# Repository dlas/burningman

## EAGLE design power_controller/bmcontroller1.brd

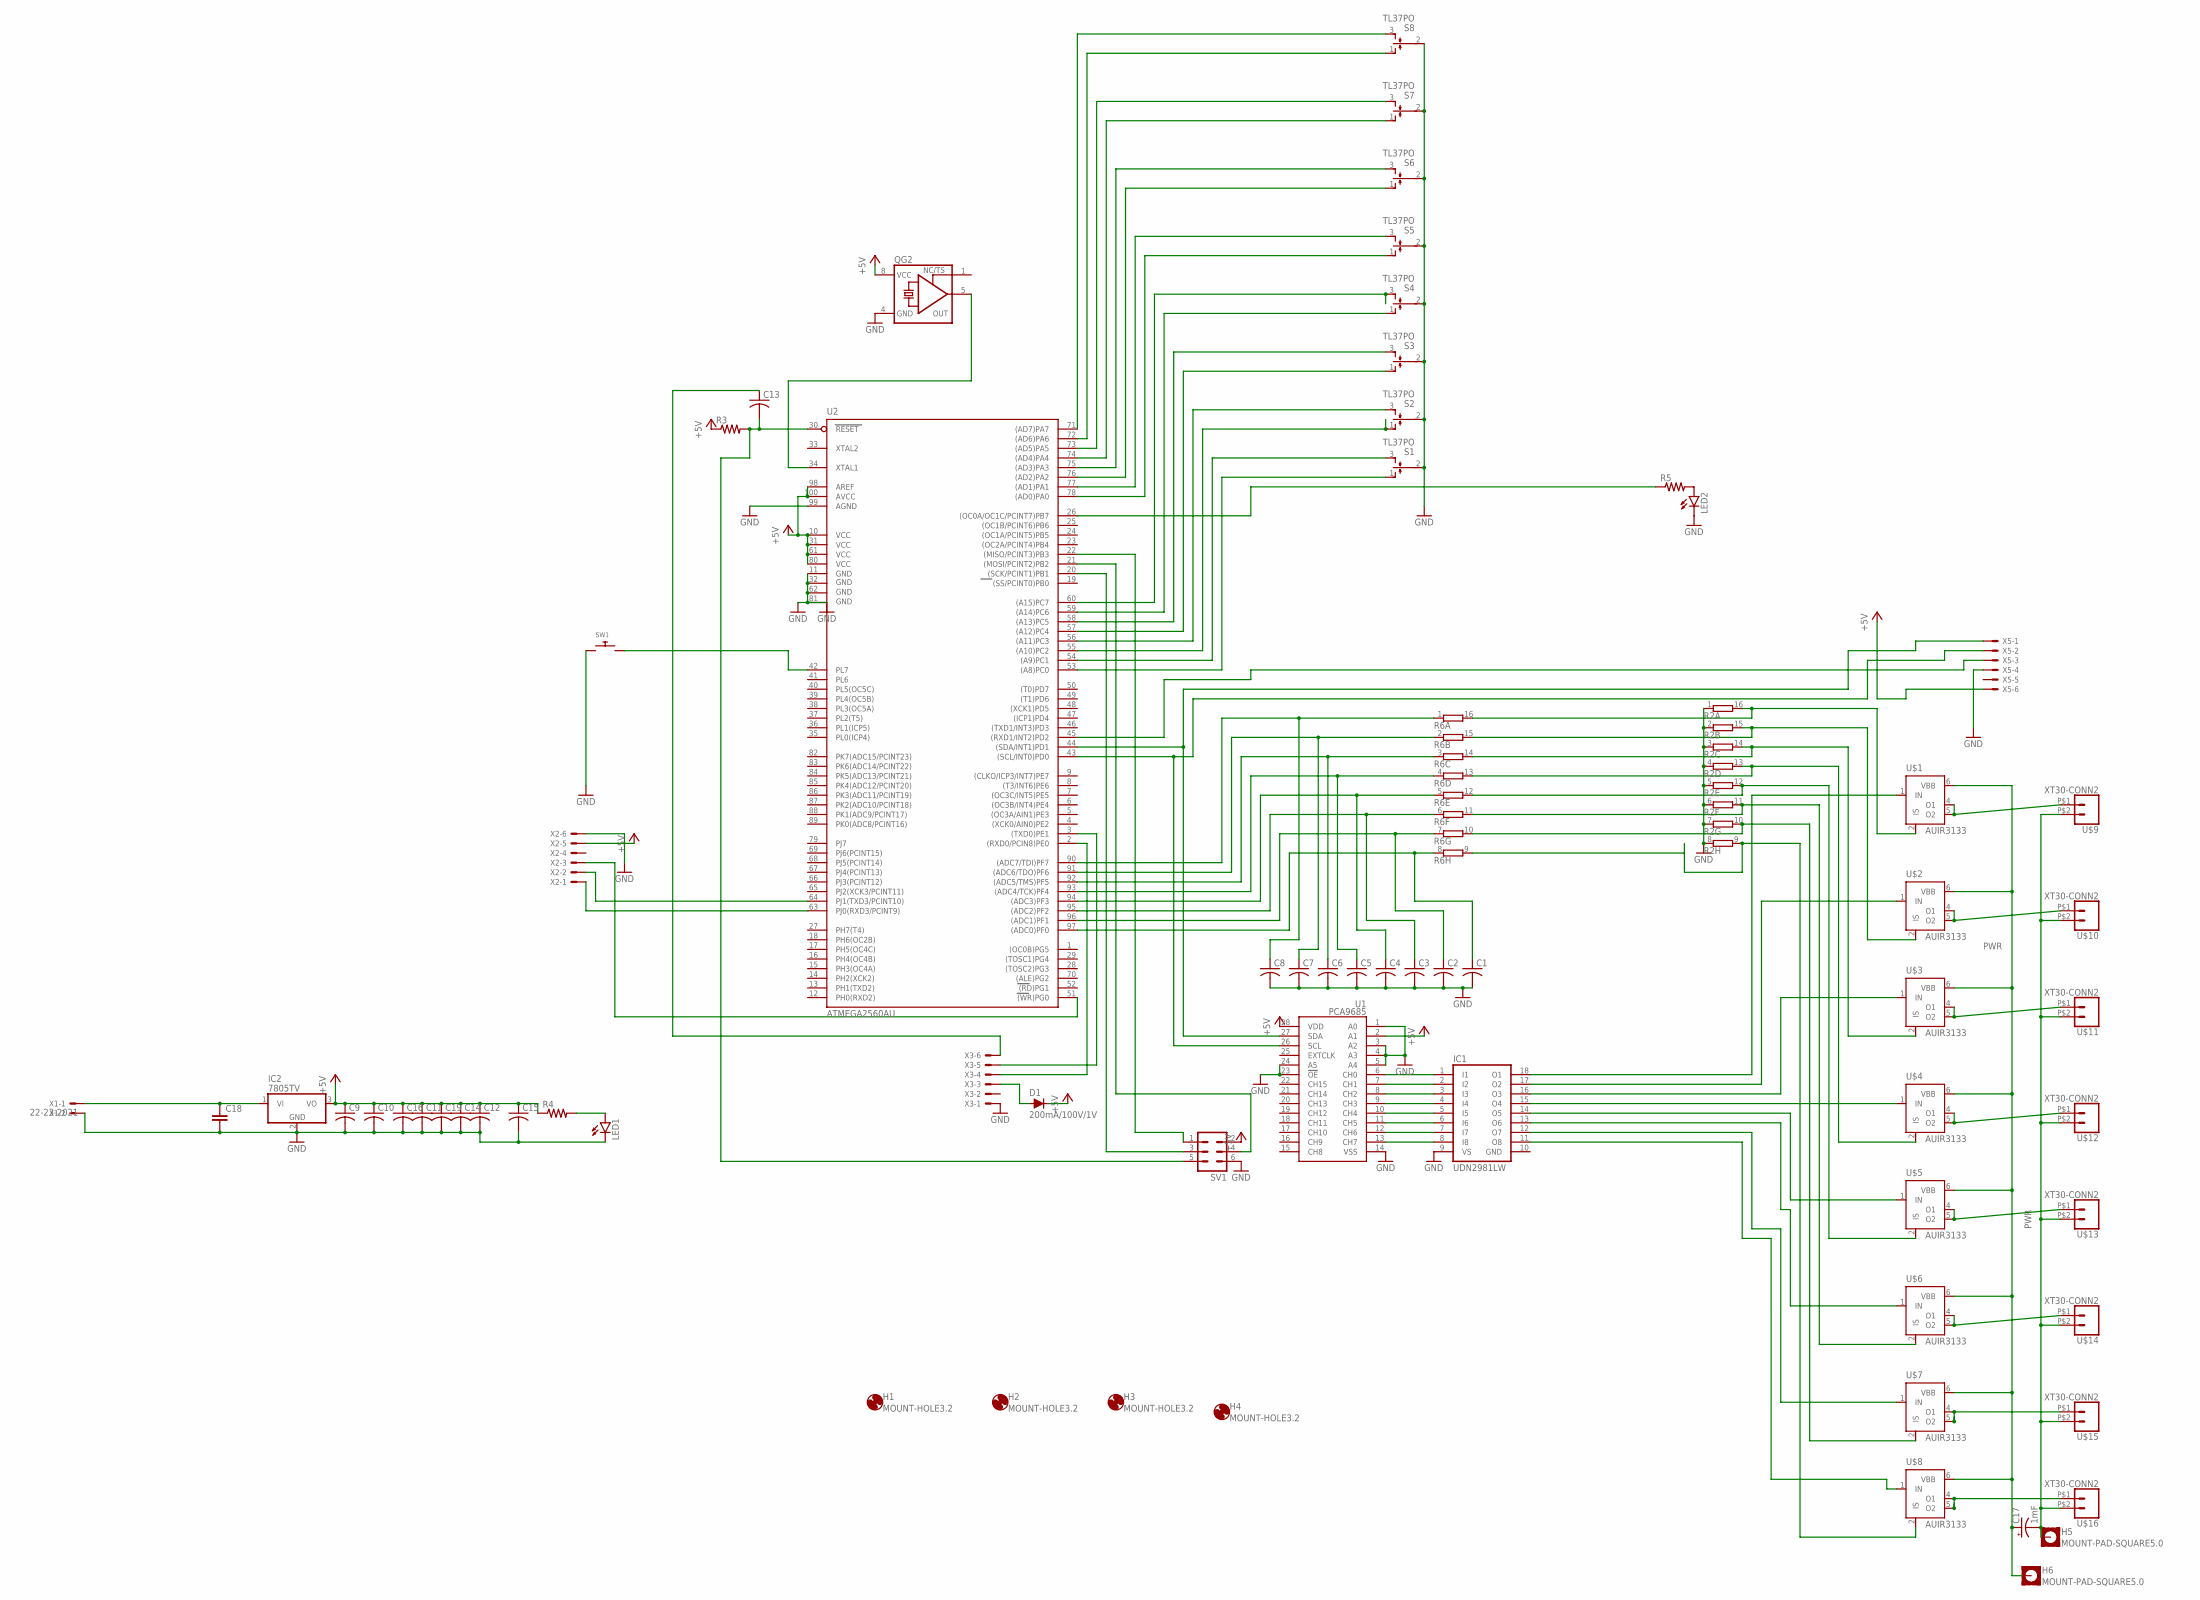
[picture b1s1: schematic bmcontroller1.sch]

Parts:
C1, C2, C3, C4, C5, C6, C7, C8, C9, C19: C-USC0805; C0805
C10, C11, C12, C13, C14, C15, C16: C-US025-024X044; C025-024X044
C17: 1mF; CPOL-RADIAL-5MM-10MM
C18: C2,5-3; C2.5-3
D1: 200mA/100V/1V; DIODE-1N4148
H1, H2, H3, H4: MOUNT-HOLE3.2; 3,2
H5, H6: MOUNT-PAD-SQUARE5.0; 5,0-PAD-SQUARE
IC1: UDN2981LW; SO18W
IC2: 7805TV; TO220V
LED1, LED2: LED3MM
QG2: XO-8; DIL08S
R2, R6: 4816P-T01E; 4816P
R3, R4, R5: R-US_R0805; R0805
S1, S2, S3, S4, S5, S6, S7, S8: TL37PO; TL3XPO
SV1: MA03-2
SW1: SWITCH_PUSHBUTTONEVQ-PE; TACT_PANA-EVQ
U1: PCA9685; TSSOP-28_4MM
U2: ATMEGA2560AU; TQFP100
U$1, U$2, U$3, U$4, U$5, U$6, U$7, U$8: AUIR3133; TO263-51
U$9, U$10, U$11, U$12, U$13, U$14, U$15, U$16: XT30-CONN2; XT30-2
X1: 22-23-2021
X2, X3, X5: 22-23-2061

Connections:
+5V: C9.1, C10.1, C11.1, C12.1, C14.1, C15.1, C16.1, C19.1, D1.C, IC2.3 (VO), QG2.8 (VCC), R3.1, R4.1, SV1.2, U1.2 (A1), U1.28 (VDD), U2.10 (VCC), U2.31 (VCC1), U2.61 (VCC2), U2.80 (VCC3), U2.98 (AREF), U2.100 (AVCC), X2.5, X5.6
BIGGND: C17.-, H5.B5, U$9.P$2 (2), U$10.P$2 (2), U$11.P$2 (2), U$12.P$2 (2), U$13.P$2 (2), U$14.P$2 (2), U$15.P$2 (2), U$16.P$2 (2)
GND: C1.2, C2.2, C3.2, C4.2, C5.2, C6.2, C7.2, C8.2, C9.2, C10.2, C11.2, C12.2, C14.2, C15.2, C16.2, C18.2, C19.2, IC1.9 (VS), IC1.10 (GND), IC2.2 (GND), LED1.K (C), LED2.K (C), QG2.4 (GND), R2.1, R2.2 (1), R2.3 (1), R2.4 (1), R2.5 (1), R2.6 (1), R2.7 (1), R2.8 (1), S1.2, S2.2, S3.2, S4.2, S5.2, S6.2, S7.2, S8.2, SV1.6, SW1.P$1, U1.1 (A0), U1.3 (A2), U1.4 (A3), U1.5 (A4), U1.14 (VSS), U1.23 (!OE), U1.24 (A5), U2.11 (GND), U2.32 (GND1), U2.62 (GND2), U2.81 (GND3), U2.99 (AGND), X1.2, X2.6, X3.1, X5.4
unnamed: C8.1, R6.1, U2.90 ((ADC7/TDI)PF7)
unnamed: C7.1, R6.2 (1), U2.91 ((ADC6/TDO)PF6)
unnamed: C6.1, R6.3 (1), U2.92 ((ADC5/TMS)PF5)
unnamed: C5.1, R6.4 (1), U2.93 ((ADC4/TCK)PF4)
unnamed: C4.1, R6.5 (1), U2.94 ((ADC3)PF3)
unnamed: C3.1, R6.6 (1), U2.95 ((ADC2)PF2)
unnamed: C2.1, R6.7 (1), U2.96 ((ADC1)PF1)
unnamed: C1.1, R6.8 (1), U2.97 ((ADC0)PF0)
unnamed: S8.1 (O), U2.72 ((AD6)PA6)
unnamed: IC1.18 (O1), U$1.1 (IN)
unnamed: IC1.14 (O5), U$5.1 (IN)
unnamed: IC1.1 (I1), U1.6 (CH0)
unnamed: R2.13 (2), R6.13 (2), U$4.2 (IS)
unnamed: R2.12 (2), R6.12 (2), U$5.2 (IS)
unnamed: R2.11 (2), R6.11 (2), U$6.2 (IS)
unnamed: R2.10 (2), R6.10 (2), U$7.2 (IS)
unnamed: R5.1, U2.26 ((OC0A/OC1C/PCINT7)PB7)
unnamed: R2.9 (2), R6.9 (2), U$8.2 (IS)
unnamed: IC1.2 (I2), U1.7 (CH1)
unnamed: IC1.3 (I3), U1.8 (CH2)
unnamed: IC1.4 (I4), U1.9 (CH3)
unnamed: QG2.5 (OUT), U2.34 (XTAL1)
unnamed: D1.A, X3.3
unnamed: S2.1 (O), U2.55 ((A10)PC2)
unnamed: C18.1, IC2.1 (VI), X1.1
unnamed: IC1.5 (I5), U1.10 (CH4)
unnamed: S4.3 (S), U2.60 ((A15)PC7)
unnamed: S8.3 (S), U2.71 ((AD7)PA7)
unnamed: SW1.P$2, U2.42 (PL7)
unnamed: S7.3 (S), U2.73 ((AD5)PA5)
unnamed: S7.1 (O), U2.74 ((AD4)PA4)
unnamed: S6.3 (S), U2.75 ((AD3)PA3)
unnamed: S6.1 (O), U2.76 ((AD2)PA2)
unnamed: LED1.A, R4.2
unnamed: C13.2, R3.2, SV1.5, U2.30 (RESET)
unnamed: SV1.1, U2.22 ((MISO/PCINT3)PB3)
unnamed: SV1.3, U2.20 ((SCK/PCINT1)PB1)
unnamed: SV1.4, U2.21 ((MOSI/PCINT2)PB2)
unnamed: C13.1, X3.6
unnamed: U2.3 ((TXD0)PE1), X3.5
unnamed: U2.2 ((RXD0/PCIN8)PE0), X3.4
unnamed: U$8.4 (O1), U$8.5 (O2), U$16.P$1 (1)
unnamed: U1.27 (SDA), U2.44 ((SDA/INT1)PD1), X5.1
unnamed: U2.63 (PJ0(RXD3/PCINT9)), X2.1
unnamed: U2.64 (PJ1(TXD3/PCINT10)), X2.2
unnamed: U2.51 ((WR)PG0), X2.3
unnamed: U1.26 (SCL), U2.43 ((SCL/INT0)PD0), X5.2
unnamed: U2.45 ((RXD1/INT2)PD2), X5.3
unnamed: U$7.4 (O1), U$7.5 (O2), U$15.P$1 (1)
unnamed: U$6.4 (O1), U$6.5 (O2), U$14.P$1 (1)
unnamed: U$5.4 (O1), U$5.5 (O2), U$13.P$1 (1)
unnamed: U$4.4 (O1), U$4.5 (O2), U$12.P$1 (1)
unnamed: U$3.4 (O1), U$3.5 (O2), U$11.P$1 (1)
unnamed: U$2.4 (O1), U$2.5 (O2), U$10.P$1 (1)
unnamed: U$1.4 (O1), U$1.5 (O2), U$9.P$1 (1)
unnamed: IC1.6 (I6), U1.11 (CH5)
unnamed: IC1.7 (I7), U1.12 (CH6)
unnamed: IC1.16 (O3), U$3.1 (IN)
unnamed: R2.14 (2), R6.14 (2), U$3.2 (IS)
unnamed: R2.15 (2), R6.15 (2), U$2.2 (IS)
unnamed: R2.16 (2), R6.16 (2), U$1.2 (IS)
unnamed: IC1.17 (O2), U$2.1 (IN)
unnamed: IC1.8 (I8), U1.13 (CH7)
unnamed: LED2.A, R5.2
unnamed: IC1.11 (O8), U$8.1 (IN)
unnamed: IC1.12 (O7), U$7.1 (IN)
unnamed: IC1.13 (O6), U$6.1 (IN)
unnamed: IC1.15 (O4), U$4.1 (IN)
unnamed: S5.3 (S), U2.77 ((AD1)PA1)
unnamed: S5.1 (O), U2.78 ((AD0)PA0)
unnamed: S4.1 (O), U2.59 ((A14)PC6)
unnamed: S3.3 (S), U2.58 ((A13)PC5)
unnamed: S3.1 (O), U2.57 ((A12)PC4)
unnamed: S2.3 (S), U2.56 ((A11)PC3)
unnamed: S1.3 (S), U2.54 ((A9)PC1)
unnamed: S1.1 (O), U2.53 ((A8)PC0)
PWR: C17.+, H6.B5, U$1.6 (VBB), U$2.6 (VBB), U$3.6 (VBB), U$4.6 (VBB), U$5.6 (VBB), U$6.6 (VBB), U$7.6 (VBB), U$8.6 (VBB)

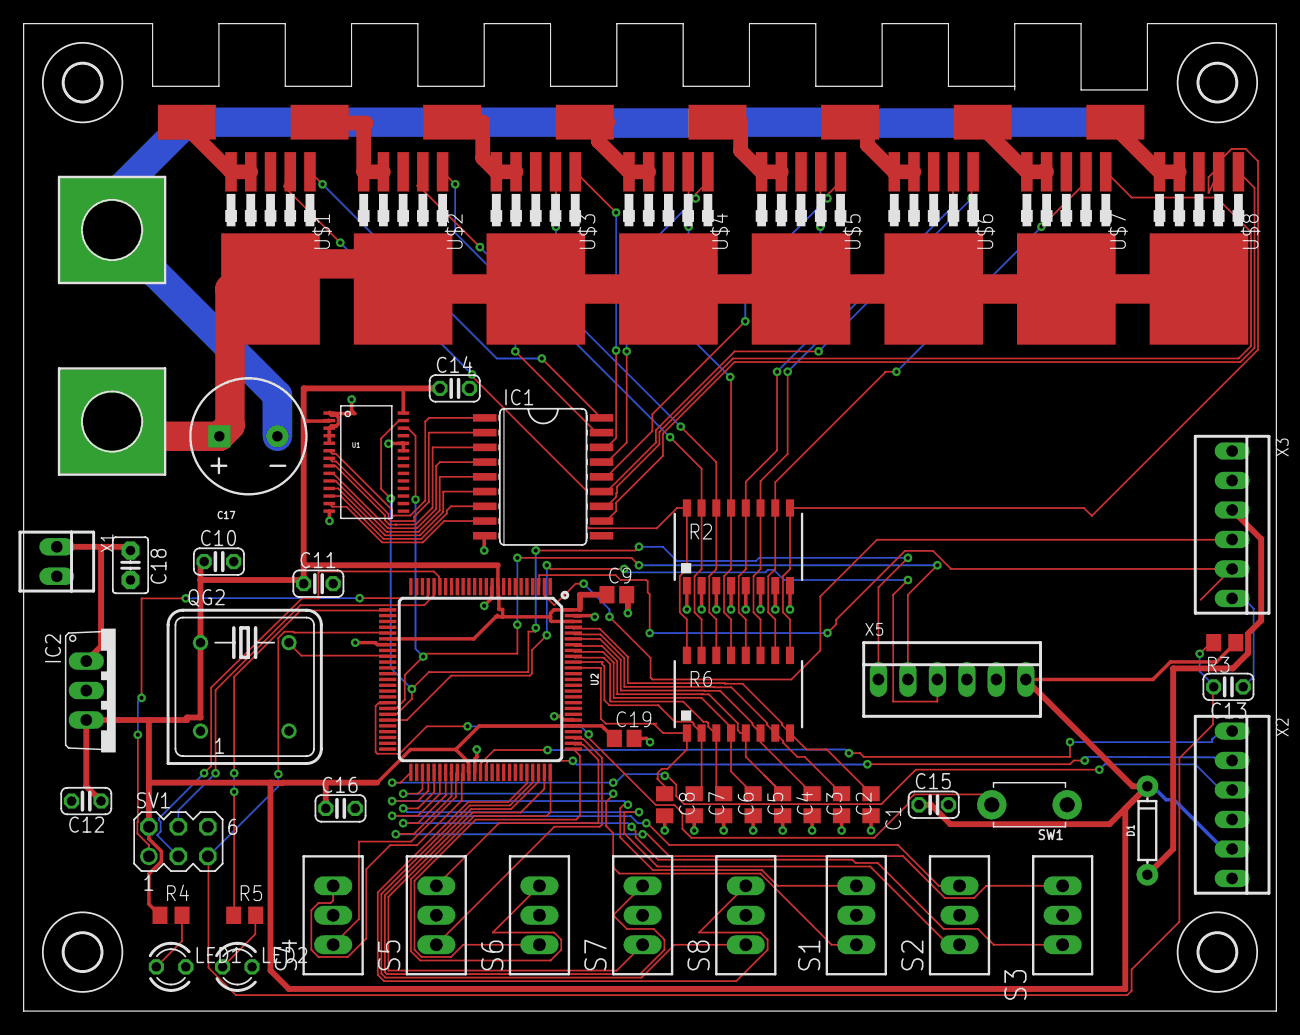
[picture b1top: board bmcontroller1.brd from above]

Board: 2 copper layers, 108.0 x 85.1 mm, 68 parts (0 on the bottom side), 80 nets.

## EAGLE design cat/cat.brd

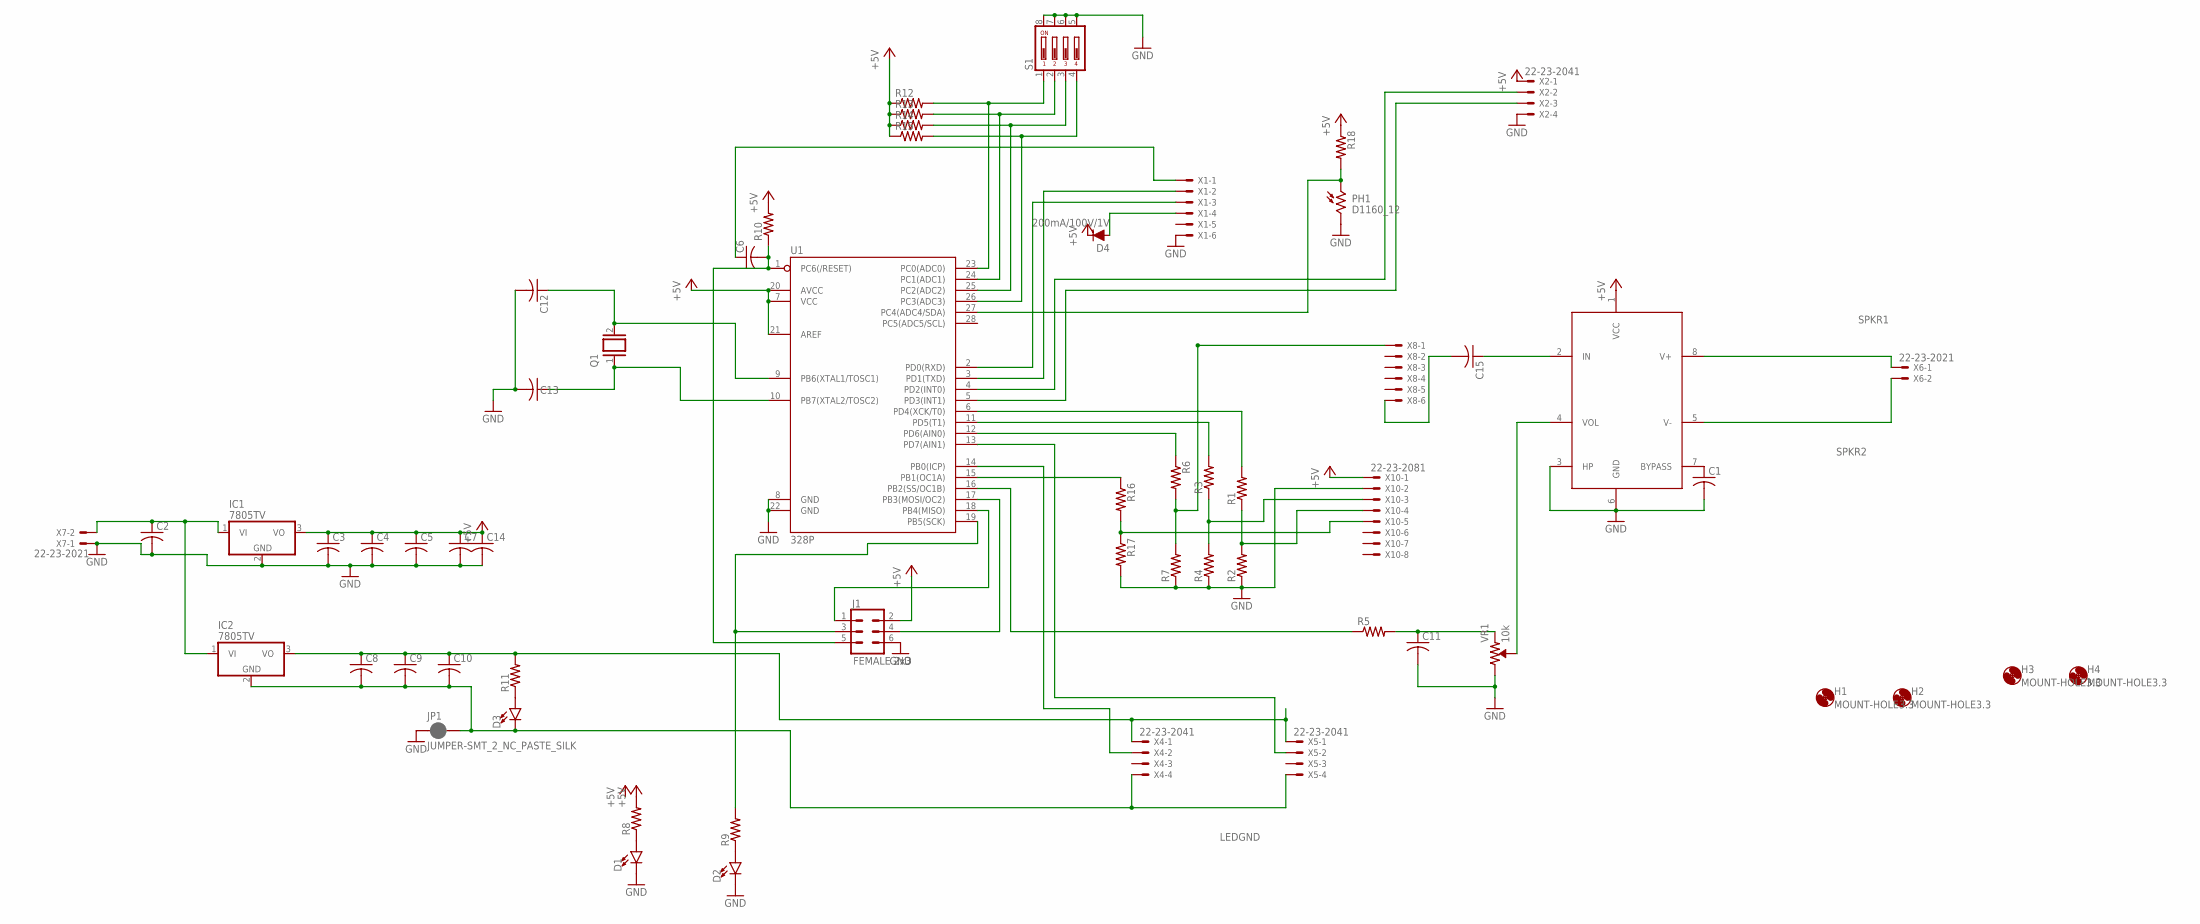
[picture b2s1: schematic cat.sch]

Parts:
C1, C2, C3, C4, C5, C6, C7, C8, C9, C10, C11, C12, C13, C14, C15: C-US025-024X044; C025-024X044
D1, D2, D3: LED-3MM-NO_SILK; LED_3MM-NS
D4: 200mA/100V/1V; DIODE-1N4148
H1, H2, H3, H4: MOUNT-HOLE3.3; 3,3
IC1, IC2: 7805TV; TO220V
J1: FEMALE 2x3; 2X3
JP1: JUMPER-SMT_2_NC_PASTE_SILK; SMT-JUMPER_2_NC_PASTE_SILK
PH1: D1160_12; D11XX
Q1: XTAL/S; QS
R1, R2, R3, R4, R5, R6, R7, R8, R9, R10, R11, R12, R13, R14, R15, R16, R17, R18: R-US_R0805; R0805
S1: DIP04YL
U1: 328P; DIP28
U$1: LM4875; SO8
VR1: 10k; TRIMPOT-PTH-3386U
X1, X8: 22-23-2061
X2, X4, X5: 22-23-2041
X6, X7: 22-23-2021
X10: 22-23-2081

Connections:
+5V: C3.1, C4.1, C5.1, C7.1, C14.1, D4.C, IC1.3 (VO), J1.2, R8.2, R10.2, R12.1, R13.1, R14.1, R15.1, R18.1, U1.7 (VCC), U1.20 (AVCC), U1.21 (AREF), U$1.1 (VCC), X2.1, X10.1
GND: C1.2, C2.2, C3.2, C4.2, C5.2, C7.2, C11.2, C12.2, C13.2, C14.2, D1.K (C), D2.K (C), IC1.2 (GND), J1.6, JP1.1, PH1.2, R2.1, R4.1, R7.1, R17.2, S1.5, S1.6, S1.7, S1.8, U1.8 (GND), U1.22 (GND), U$1.3 (HP), U$1.6 (GND), VR1.3 (CW), X1.6, X2.4, X7.1, X10.2
INPWR: C2.1, IC1.1 (VI), IC2.1 (VI), X7.2
LEDGND: C8.2, C9.2, C10.2, D3.K (C), IC2.2 (GND), JP1.2, X4.4, X5.4
LEDPWR: C8.1, C9.1, C10.1, IC2.3 (VO), R11.2, X4.1, X5.1
unnamed: R1.1, R2.2, X10.4
unnamed: R1.2, U1.6 (PD4(XCK/T0))
unnamed: R3.2, U1.11 (PD5(T1))
unnamed: C15.2, X8.6
unnamed: R3.1, R4.2, X10.3
unnamed: R6.2, R7.2, X8.1
unnamed: J1.3, R9.2, U1.19 (PB5(SCK))
unnamed: R6.1, U1.12 (PD6(AIN0))
unnamed: J1.1, U1.18 (PB4(MISO))
unnamed: J1.4, U1.17 (PB3(MOSI/OC2))
unnamed: R5.1, U1.16 (PB2(SS/OC1B))
unnamed: U1.13 (PD7(AIN1)), X5.2
unnamed: U$1.4 (VOL), VR1.2 (WIPER)
unnamed: U1.14 (PB0(ICP)), X4.2
unnamed: R16.1, U1.15 (PB1(OC1A))
unnamed: C1.1, U$1.7 (BYPASS)
unnamed: C13.1, Q1.1, U1.10 (PB7(XTAL2/TOSC2))
unnamed: C11.1, R5.2, VR1.1 (CCW)
unnamed: R12.2, S1.1, U1.23 (PC0(ADC0))
unnamed: C6.2, J1.5, R10.1, U1.1 (PC6(/RESET))
unnamed: R13.2, S1.2, U1.24 (PC1(ADC1))
unnamed: C6.1, X1.1
unnamed: U1.2 (PD0(RXD)), X1.3
unnamed: U1.3 (PD1(TXD)), X1.2
unnamed: D2.A, R9.1
unnamed: D1.A, R8.1
unnamed: R14.2, S1.3, U1.25 (PC2(ADC2))
unnamed: D3.A, R11.1
unnamed: R15.2, S1.4, U1.26 (PC3(ADC3))
unnamed: C12.1, Q1.2, U1.9 (PB6(XTAL1/TOSC1))
unnamed: U1.4 (PD2(INT0)), X2.2
unnamed: U1.5 (PD3(INT1)), X2.3
unnamed: D4.A, X1.4
unnamed: R16.2, R17.1, X10.5
unnamed: C15.1, U$1.2 (IN)
unnamed: PH1.1, R18.2, U1.27 (PC4(ADC4/SDA))
SPKR1: U$1.8 (V+), X6.1
SPKR2: U$1.5 (V-), X6.2

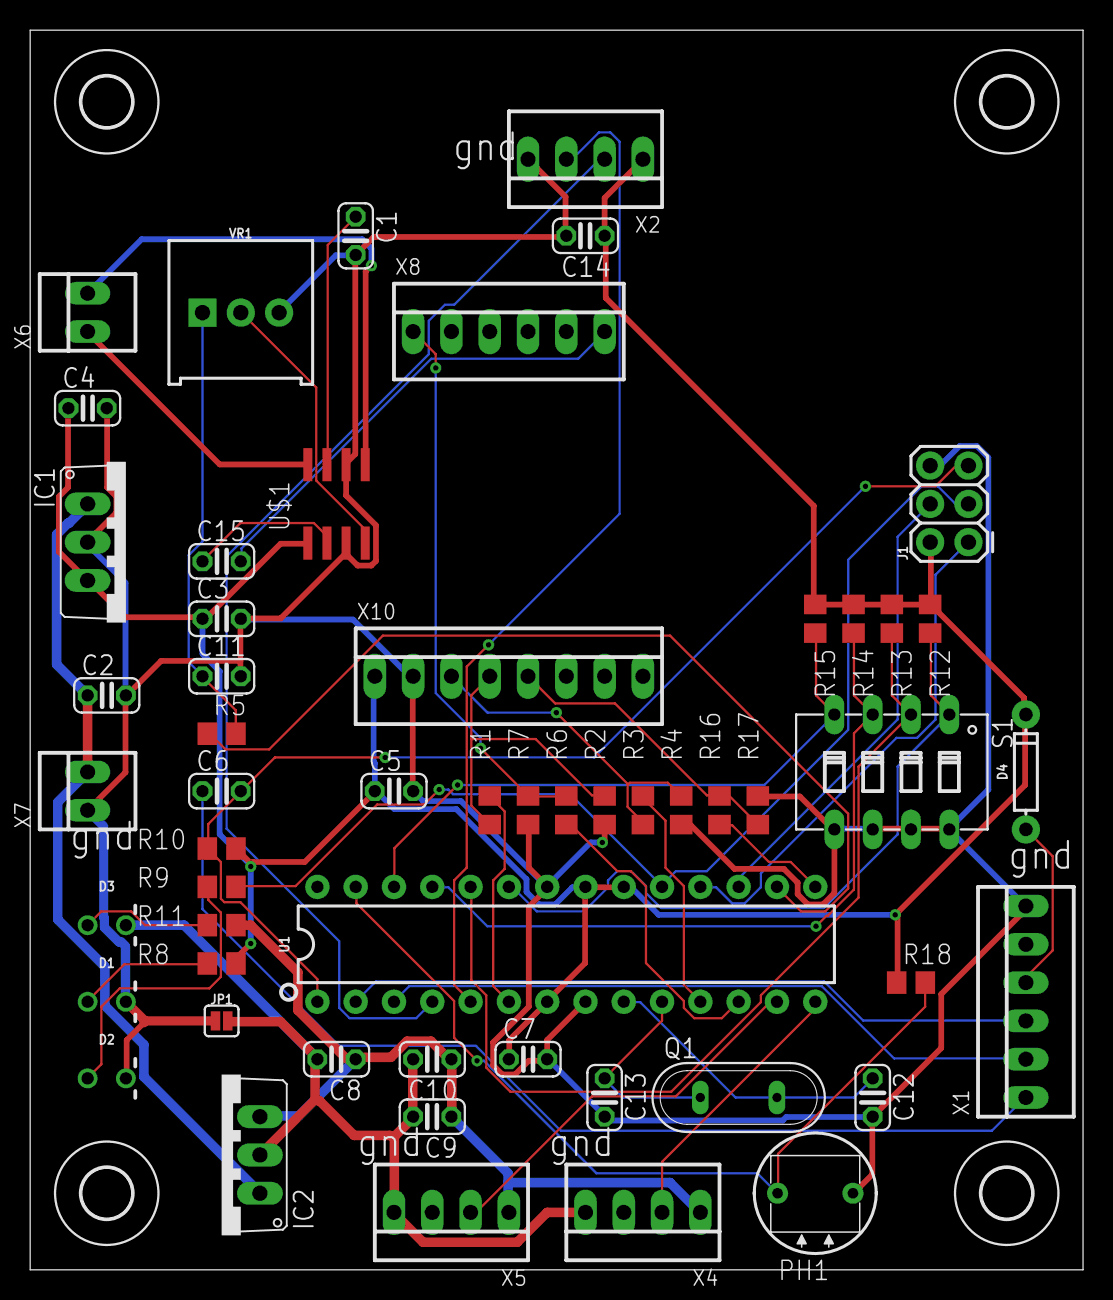
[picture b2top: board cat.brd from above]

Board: 2 copper layers, 69.8 x 82.2 mm, 59 parts (0 on the bottom side), 43 nets.

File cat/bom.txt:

C1	1.0uF
C2	47uF
C3	22uF
C4	0.1uF
C5	1.0uF
C6 	0.1uF
C7	0.1uF
C8	22uF
C9	2.2uF
10	2.2uF
C11	0.1uF
C12	22pF
C13	22pF
C14	2.2uF
C15	2.2uF

R1	4.7K
R2	10K
R3	4.7K
R4	10K
R5	1K
R6	4.7K
R7	10K
R8	1K
R9	1K
R10	10K
R11	1K
R12	10K
R13	10K
R14	10K
R15	10K
R16	4.7K
R17	10K
R18	10K

Q1	16MHZ

D1	Green
D2	Red
D3	Yellow

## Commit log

2019-05-16 Initial commit.
2019-05-16 Add cat board schematics.
2019-05-16 Add cat code
2019-05-16 Add firmware, schematics, pinout for power control boards.
2019-05-16 Add location of components in PDU controller.
2019-05-23 Oopss. Things get darker at night!
2019-05-27 Add code for big light pyramid thing.
2019-05-27 Add some code to handle the pyramid topology.
2019-05-28 big lights thing: Fix a bunch of little mistakes in the graph representation of the pyramin. Things now line up now.
    cat lights: Don't infinite loop if the ultrasonic sensor never responds. Adjust light levels
2019-06-01 Add initial dimmer support.
2019-06-01 Make knobs work
2019-06-01 Add a new crazy pants mode with allthe colors and stuff.
2019-06-02 Add a new idea.
2019-06-02 cosmetic fixes
2019-06-08 Squashed commit of the following:
    commit 326dec83f561056d33ade21440f40dd0cb09d9d9
    Author: David Stafford <dstaff@kalexland.com>
    Date: Fri Jun 7 19:09:47 2019 -0700
    Add code for light, bike, lights, etc
    commit e3738fe4ab2877a49effee7cd82c5297d551a61e
    Author: David Stafford <dstaff@kalexland.com>
2019-06-15 Some temporary cat adjustments;
    add more clock stuff to the PDU
2019-07-07 Implement a bunch more light patterns on the cats. Use the DIP switches to select the pattern. More adjustments to daylight sensors. Stop locking the system up when it detects a human.
2019-07-07 Add another mode to the pyramid.
2019-07-15 timer fixes.
2019-07-15 add hold off cat sound effect
2019-07-17 new modes for pyramid
2019-07-25 changes to belt, hat code to disable anklets.
2019-07-25 Add super simple code for belt
2019-08-20 add some pins

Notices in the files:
parts and their libraries:
SparkFun-IC-Microcontroller: Licensing: Creative Commons ShareAlike 4.0 International - https://creativecommons.org/licenses/by-sa/4.0
